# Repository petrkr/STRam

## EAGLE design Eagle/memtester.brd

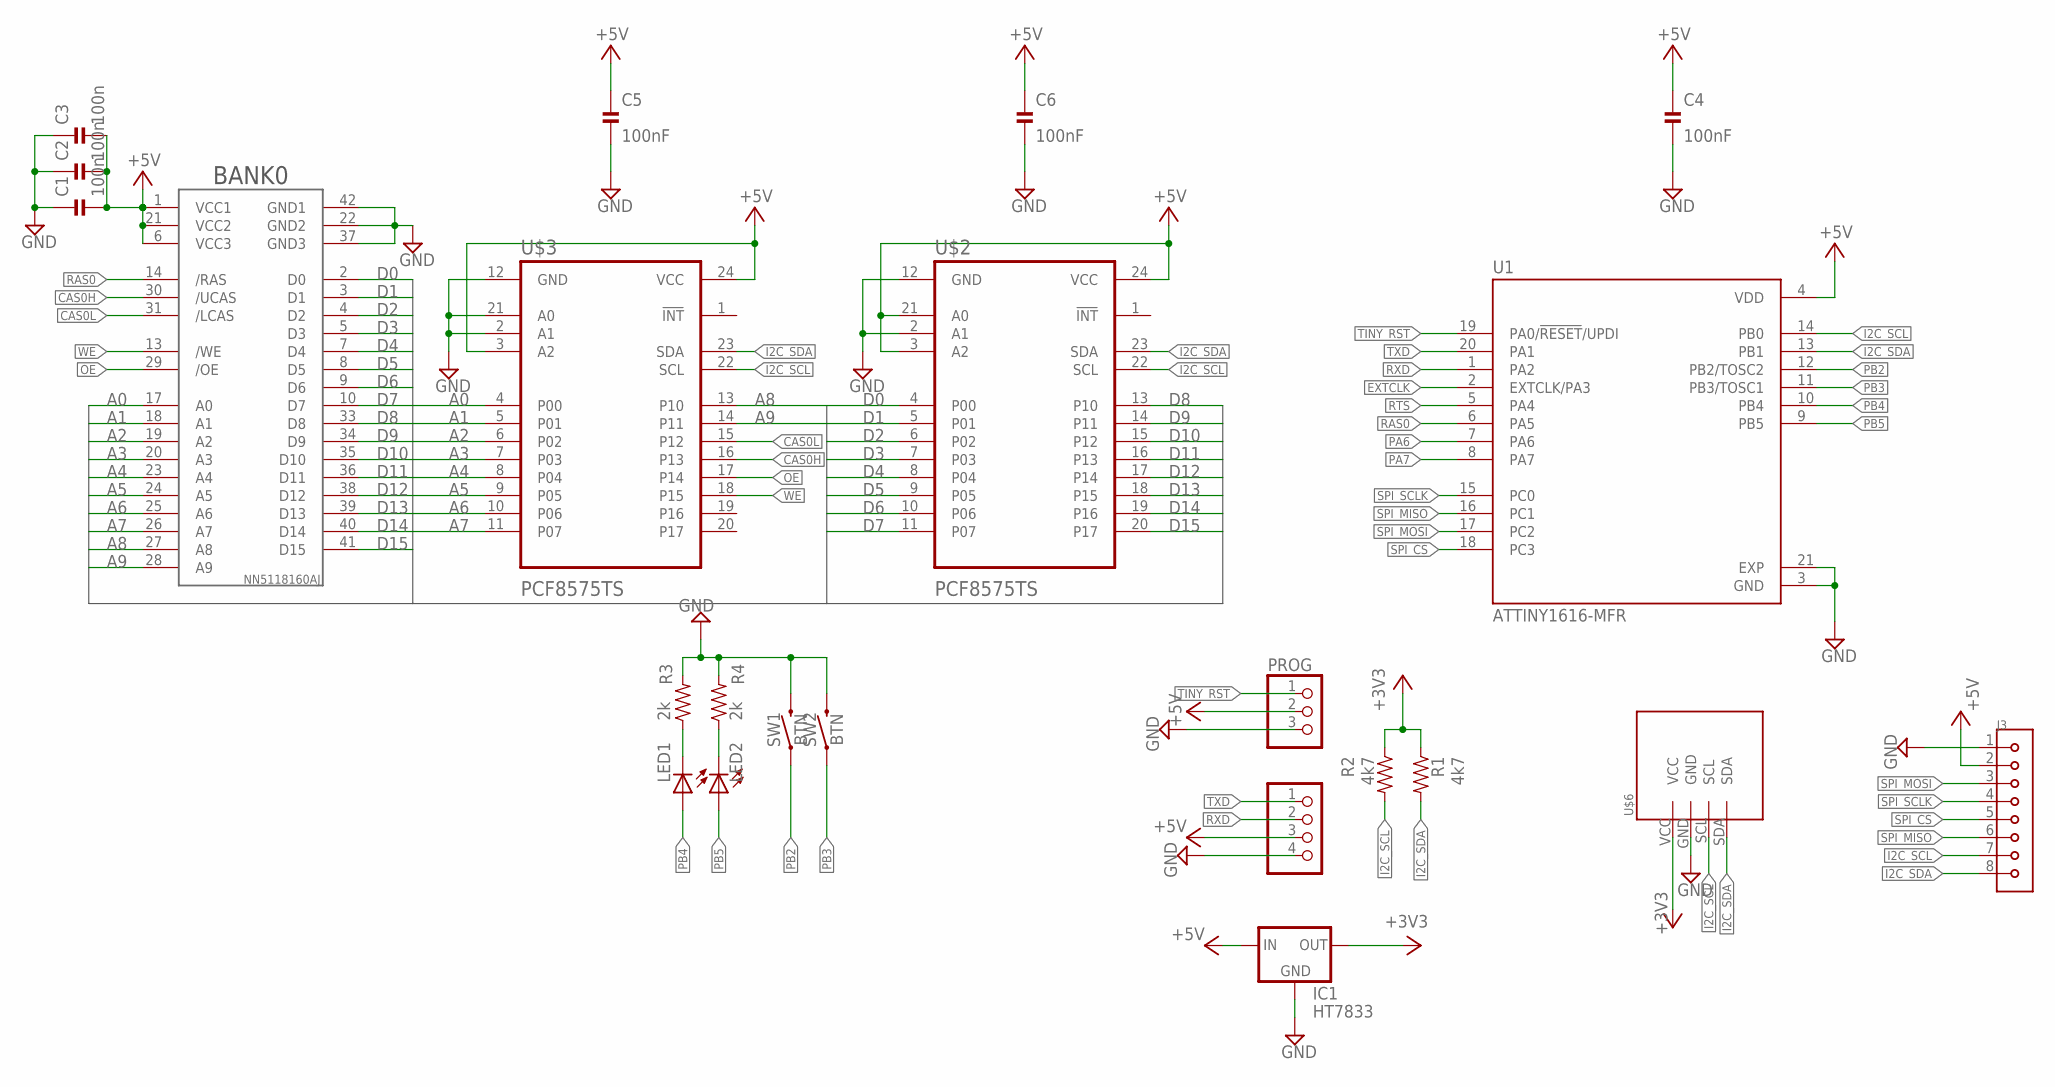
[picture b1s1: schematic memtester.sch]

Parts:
C1, C2, C3: 100n; 0402_CAP
C4, C5, C6: 100nF; 0402_CAP
IC1: HT7833; SOT-89; LCSC_PART C50936
J3: SM08B-SRSS-TB(LF)(SN); JST_SM08B-SRSS-TB(LF)(SN); LCSC_PART C160407
LED1, LED2: green; CHIP-LED0805; LCSC_PART C2297
PROG: PINHD-1X3; 1X03
R1, R2: 4k7; 0402_RES
R3, R4: 2k; 0402_RES
SW1, SW2: BTN; TACTILE_SWITCH_SMD_6.0X3.5MM; LCSC_PART C118141
U1: ATTINY1616-MFR; QFN40P300X300X90-21N
U$1: NN5118160AJSOCKET; SOJ42SOCKET
U$2, U$3: PCF8575TS; SSOP24; LCSC_PART C12251
U$6: OLED_0.96_I2CNO_DRILL; OLED_0.96_I2C_NO_DRILL
UART: PINHD-1X4; 1X04

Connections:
+3V3: IC1.1 (OUT), R1.1, R2.1, U$6.VCC
+5V: C1.2, C2.2, C3.2, C4.1, C5.1, C6.1, IC1.3 (IN), IC1.4 (IN), J3.2, PROG.2, U1.4 (VDD), U$1.1 (VCC1), U$1.6 (VCC3), U$1.21 (VCC2), U$2.3 (A2), U$2.21 (A0), U$2.24 (VCC), U$3.3 (A2), U$3.24 (VCC), UART.3
A0: U$1.17 (A0), U$3.4 (P00)
A1: U$1.18 (A1), U$3.5 (P01)
A2: U$1.19 (A2), U$3.6 (P02)
A3: U$1.20 (A3), U$3.7 (P03)
A4: U$1.23 (A4), U$3.8 (P04)
A5: U$1.24 (A5), U$3.9 (P05)
A6: U$1.25 (A6), U$3.10 (P06)
A7: U$1.26 (A7), U$3.11 (P07)
A8: U$1.27 (A8), U$3.13 (P10)
A9: U$1.28 (A9), U$3.14 (P11)
CAS0H: U$1.30 (/UCAS), U$3.16 (P13)
CAS0L: U$1.31 (/LCAS), U$3.15 (P12)
D0: U$1.2 (D0), U$2.4 (P00)
D1: U$1.3 (D1), U$2.5 (P01)
D2: U$1.4 (D2), U$2.6 (P02)
D3: U$1.5 (D3), U$2.7 (P03)
D4: U$1.7 (D4), U$2.8 (P04)
D5: U$1.8 (D5), U$2.9 (P05)
D6: U$1.9 (D6), U$2.10 (P06)
D7: U$1.10 (D7), U$2.11 (P07)
D8: U$1.33 (D8), U$2.13 (P10)
D9: U$1.34 (D9), U$2.14 (P11)
D10: U$1.35 (D10), U$2.15 (P12)
D11: U$1.36 (D11), U$2.16 (P13)
D12: U$1.38 (D12), U$2.17 (P14)
D13: U$1.39 (D13), U$2.18 (P15)
D14: U$1.40 (D14), U$2.19 (P16)
D15: U$1.41 (D15), U$2.20 (P17)
EXTCLK: U1.2 (EXTCLK/PA3)
GND: C1.1, C2.1, C3.1, C4.2, C5.2, C6.2, IC1.2 (GND), J3.1, PROG.3, R3.2, R4.2, SW1.2, SW2.2, U1.3 (GND), U1.21 (EXP), U$1.22 (GND2), U$1.37 (GND3), U$1.42 (GND1), U$2.2 (A1), U$2.12 (GND), U$3.2 (A1), U$3.12 (GND), U$3.21 (A0), U$6.GND, UART.4
I2C_SCL: J3.7, R2.2, U1.14 (PB0), U$2.22 (SCL), U$3.22 (SCL), U$6.SCL
I2C_SDA: J3.8, R1.2, U1.13 (PB1), U$2.23 (SDA), U$3.23 (SDA), U$6.SDA
unnamed: LED1.C, R3.1
unnamed: LED2.C, R4.1
OE: U$1.29 (/OE), U$3.17 (P14)
PA6: U1.7 (PA6)
PA7: U1.8 (PA7)
PB2: SW1.1, U1.12 (PB2/TOSC2)
PB3: SW2.1, U1.11 (PB3/TOSC1)
PB4: LED1.A, U1.10 (PB4)
PB5: LED2.A, U1.9 (PB5)
RAS0: U1.6 (PA5), U$1.14 (/RAS)
RTS: U1.5 (PA4)
RXD: U1.1 (PA2), UART.2
SPI_CS: J3.5, U1.18 (PC3)
SPI_MISO: J3.6, U1.16 (PC1)
SPI_MOSI: J3.3, U1.17 (PC2)
SPI_SCLK: J3.4, U1.15 (PC0)
TINY_RST: PROG.1, U1.19 (PA0/!RESET!/UPDI)
TXD: U1.20 (PA1), UART.1
WE: U$1.13 (/WE), U$3.18 (P15)

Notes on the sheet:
BANK0

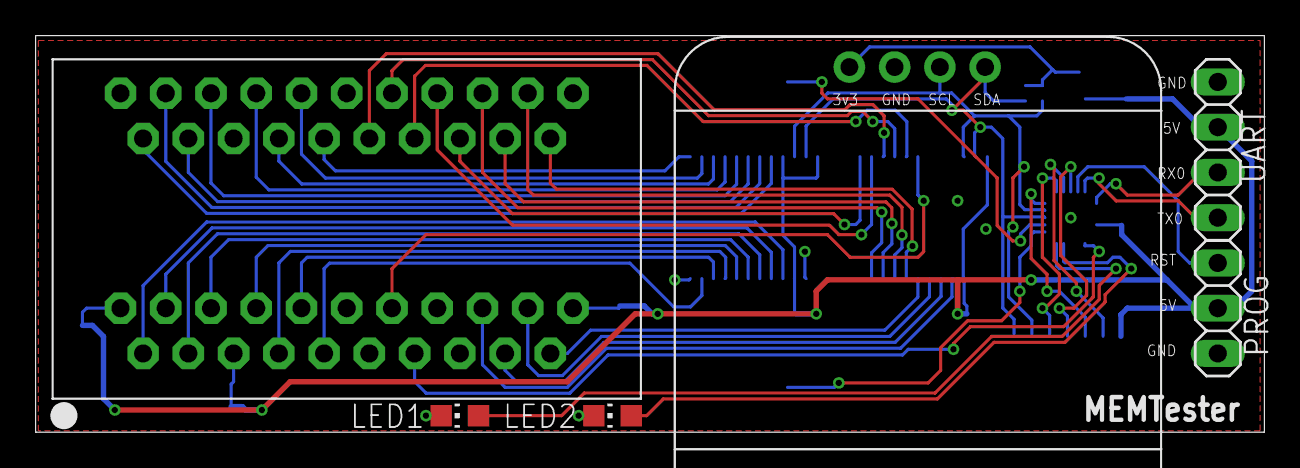
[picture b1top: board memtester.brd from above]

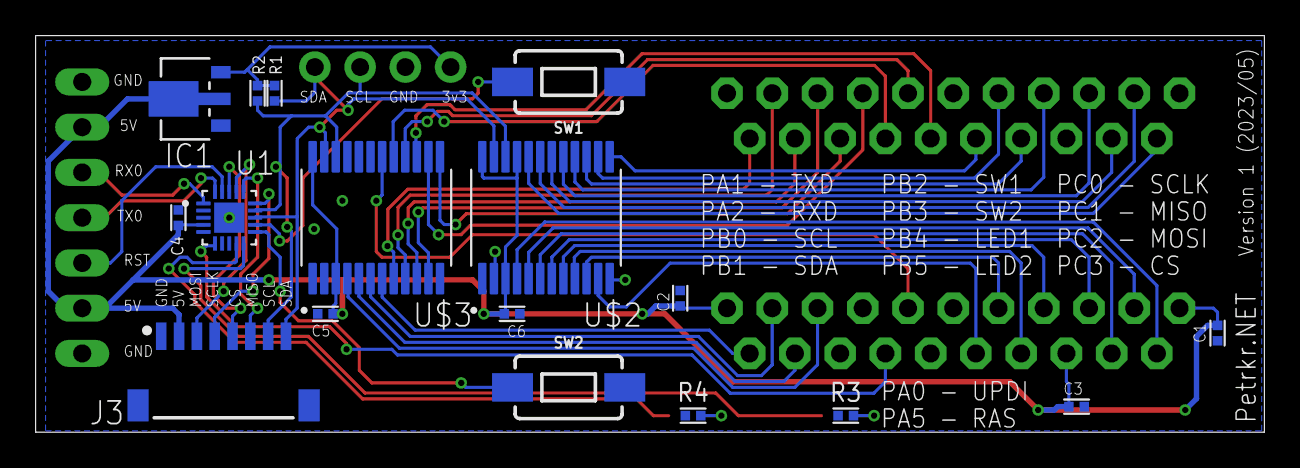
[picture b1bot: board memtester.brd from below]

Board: 2 copper layers, 69.0 x 22.3 mm, 23 parts (17 on the bottom side), 49 nets.

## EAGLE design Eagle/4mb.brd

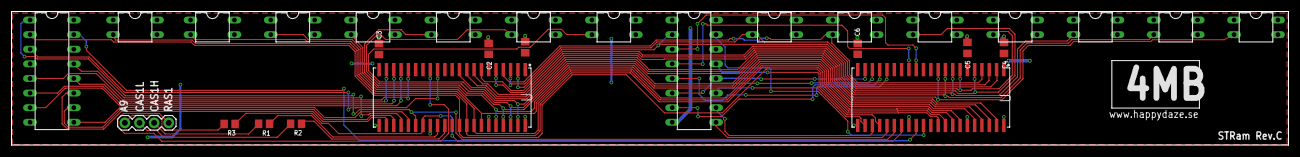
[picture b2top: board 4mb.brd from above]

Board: 2 copper layers, 222.0 x 23.2 mm, 28 parts (0 on the bottom side), 38 nets.

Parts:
C1, C2, C3, C4, C5, C6: C0805
J1: 1X04
R1, R2: 68; R0805
R3: 33; R0805
U$1, U$2: NN5118160AJ; SOJ127P1117X376-42
U$3, U$11: ST_DRAM; DIL16
U$4, U$5, U$6, U$7, U$8, U$9, U$10, U$12, U$13, U$14, U$15, U$16, U$17, U$18: ST_DRAM_D; ST_DRAM_SOCKET_MINIMAL

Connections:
+5V: C1.2, C2.2, C3.2, C4.2, C5.2, C6.2, U$1.1, U$1.6, U$1.21, U$2.1, U$2.6, U$2.21, U$3.8, U$11.8
A0: U$1.17, U$2.17, U$3.5, U$11.5
A1: U$1.18, U$2.18, U$3.7, U$11.7
A2: U$1.19, U$2.19, U$3.6, U$11.6
A3: U$1.20, U$2.20, U$3.12, U$11.12
A4: U$1.23, U$2.23, U$3.11, U$11.11
A5: U$1.24, U$2.24, U$3.10, U$11.10
A6: U$1.25, U$2.25, U$3.13, U$11.13
A7: U$1.26, U$2.26, U$3.9, U$11.9
A8: U$1.27, U$2.27, U$3.1, U$11.1
A9: R3.2, U$1.28, U$2.28
CAS0H: U$1.30, U$3.15
CAS0L: U$1.31, U$11.15
CAS1H: R1.2, U$2.30
CAS1L: R2.2, U$2.31
D0: U$1.2, U$2.2, U$11.2
D1: U$1.3, U$2.3, U$12.2
D2: U$1.4, U$2.4, U$13.2
D3: U$1.5, U$2.5, U$14.2
D4: U$1.7, U$2.7, U$15.2
D5: U$1.8, U$2.8, U$16.2
D6: U$1.9, U$2.9, U$17.2
D7: U$1.10, U$2.10, U$18.2
D8: U$1.33, U$2.33, U$3.2
D9: U$1.34, U$2.34, U$4.2
D10: U$1.35, U$2.35, U$5.2
D11: U$1.36, U$2.36, U$6.2
D12: U$1.38, U$2.38, U$7.2
D13: U$1.39, U$2.39, U$8.2
D14: U$1.40, U$2.40, U$9.2
D15: U$1.41, U$2.41, U$10.2
GND: C1.1, C2.1, C3.1, C4.1, C5.1, C6.1, U$1.22, U$1.29, U$1.37, U$1.42, U$2.22, U$2.29, U$2.37, U$2.42, U$3.16, U$4.16, U$5.16, U$6.16, U$7.16, U$8.16, U$9.16, U$10.16, U$11.16, U$12.16, U$13.16, U$14.16, U$15.16, U$16.16, U$17.16, U$18.16
unnamed: J1.2, R2.1
unnamed: J1.1, R3.1
unnamed: J1.3, R1.1
RAS0: U$1.14, U$11.4
RAS1: J1.4, U$2.14
WE: U$1.13, U$2.13, U$3.3, U$11.3

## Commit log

2022-09-21 Routed CAS0H
2022-09-21 Board rev.C
2022-09-21 Updated gerber files to Rev.C
2023-05-24 Memtester initial commit
2023-05-24 Library for memory, initial commit
2023-05-24 Memtester: part work backup
2023-05-25 Memtester: part work
2023-05-25 Memtester: routed RAS0
2023-05-25 Memtester: bigger 5v wire
2023-05-25 Memtester: i2c pull-ups, labels, credits
2023-05-25 Memtester: leds, button
2023-05-25 Memtester: Labels, wirestubs
2023-06-09 Memtester: C values
2023-06-09 Library: memory socket

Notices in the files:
parts and their libraries:
SparkFun-Connectors: Licensing: Creative Commons ShareAlike 4.0 International - https://creativecommons.org/licenses/by-sa/4.0
